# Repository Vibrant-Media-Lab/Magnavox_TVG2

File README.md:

# Ralph Baer's TV Game Version 2

Ralph Henry Baer, "the Father of Video Games", engineered the first home video game console, licensed by Magnavox as the Magnavox Odyssey.
Before the Odyssey came along, there were 3 prototypes, named TV Game 1, TV Game 2 and TV Game 3 "The Brown Box". The world famous Atari 
game _"Pong"_ is inspired by the _Table Tennis_ game available on the Brown Box and Odyssey.

This repository contains a true-to-original replica of the TV Game 2 video game console, drafted by Ralph in 1967. Thanks to the support from 
the Smithsonian Institute, we are able to obtain the original paper-based schematics, game overlays and an enclosure replica.

The finished unit will be on display in University of Pittsburgh's Vibrant Media Lab, headed by Dr. Zachary Horton.

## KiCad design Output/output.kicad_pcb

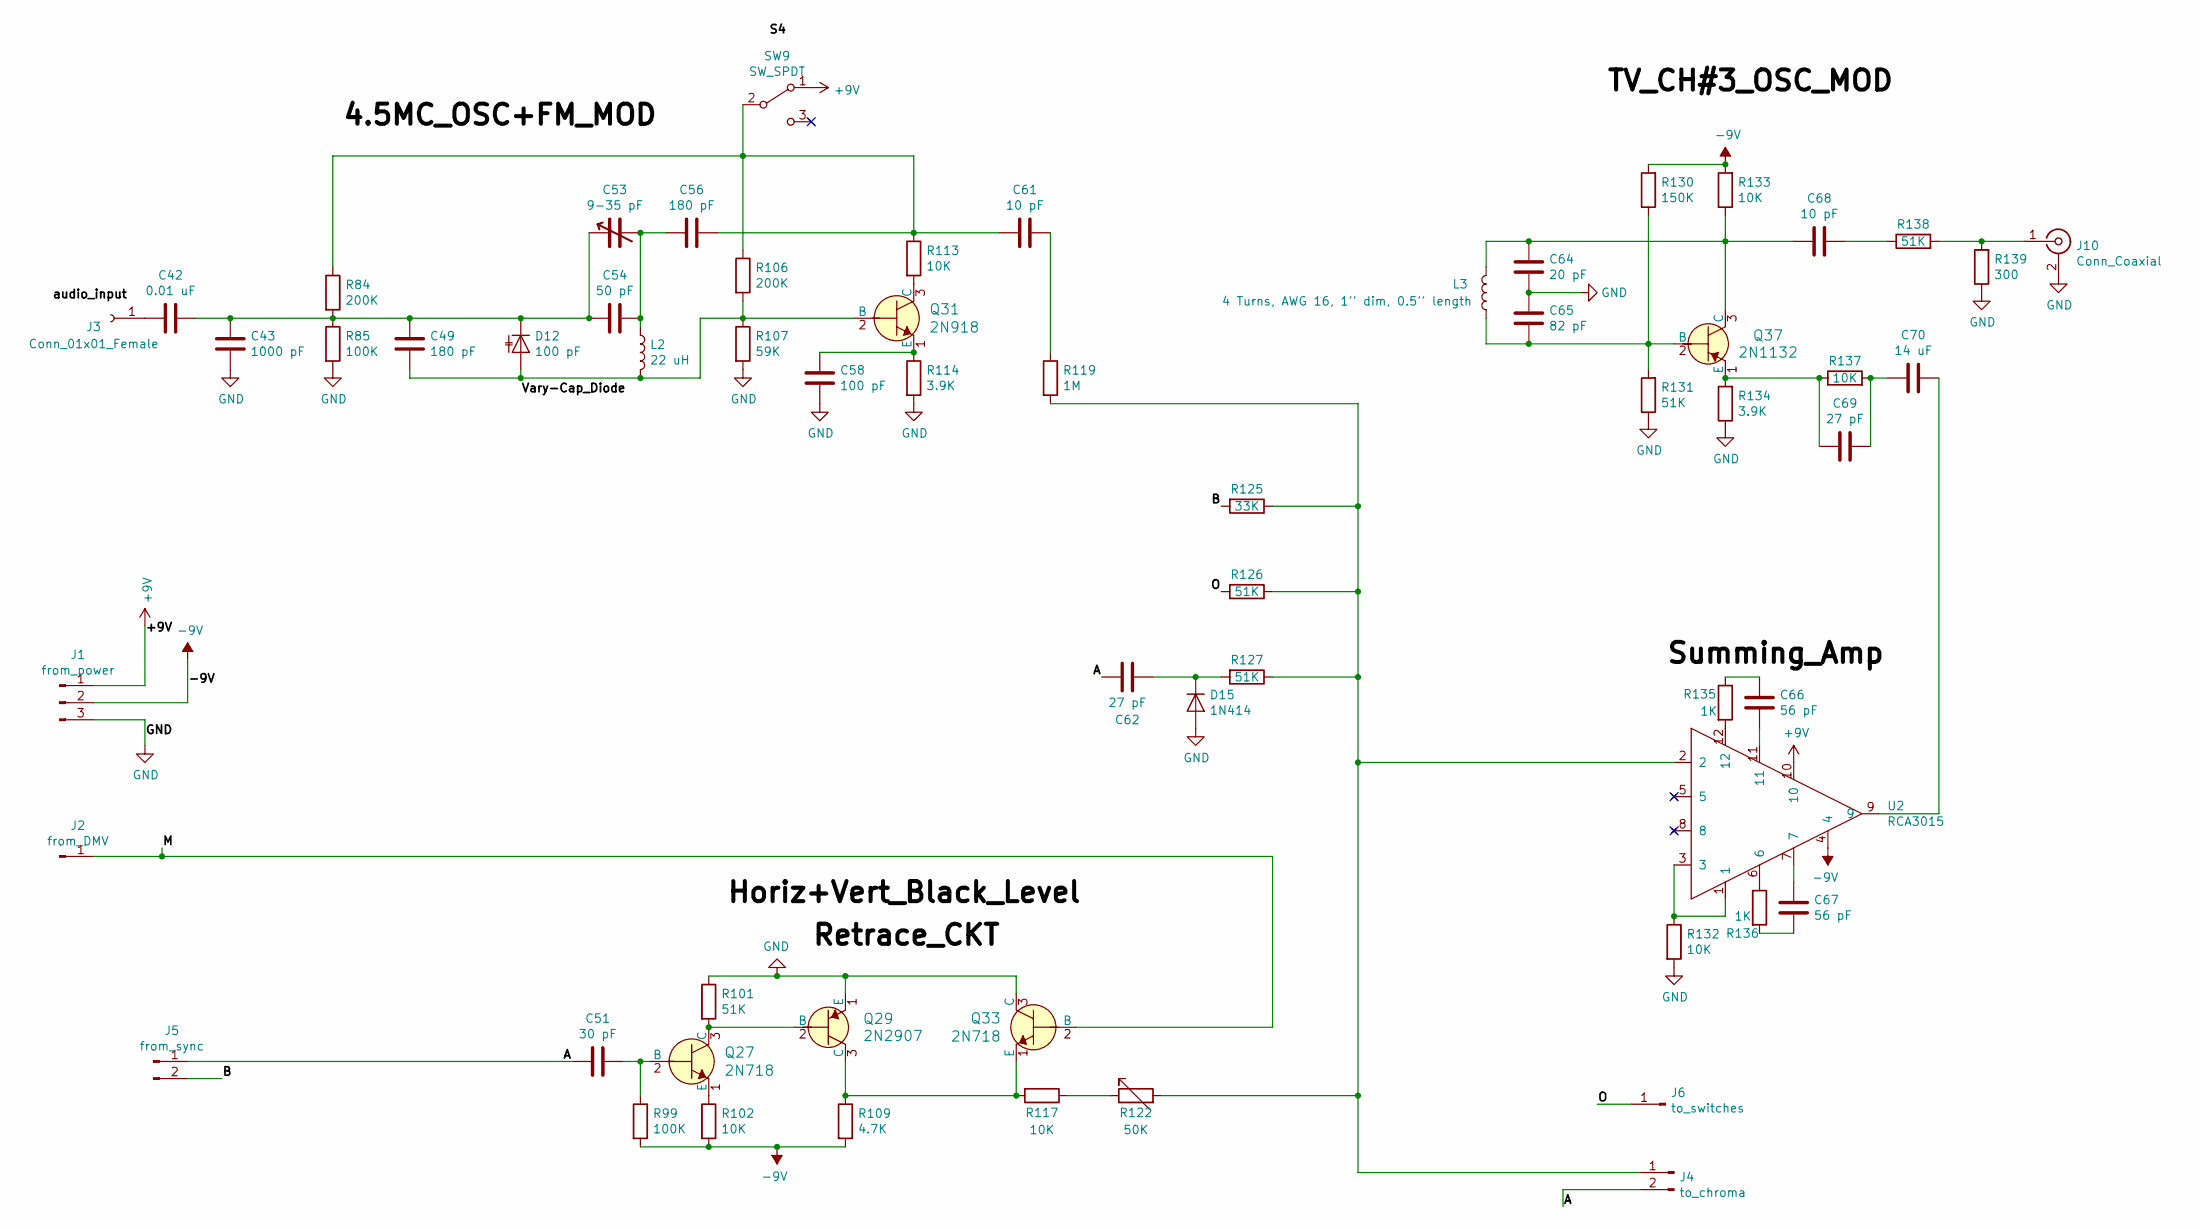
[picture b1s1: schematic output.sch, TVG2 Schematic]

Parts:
C42: 0.01 uF; C_Disc_D4.7mm_W2.5mm_P5.00mm
C43: 1000 pF; C_Disc_D4.7mm_W2.5mm_P5.00mm
C49, C56: 180 pF; C_Disc_D4.7mm_W2.5mm_P5.00mm
C51: 30 pF; C_Disc_D4.7mm_W2.5mm_P5.00mm
C53: 9-35 pF; 9-35pF_Trim
C54: 50 pF; C_Disc_D4.7mm_W2.5mm_P5.00mm
C58: 100 pF; C_Disc_D4.7mm_W2.5mm_P5.00mm
C61, C68: 10 pF; C_Disc_D4.7mm_W2.5mm_P5.00mm
C62, C69: 27 pF; C_Disc_D4.7mm_W2.5mm_P5.00mm
C64: 20 pF; C_Disc_D4.7mm_W2.5mm_P5.00mm
C65: 82 pF; C_Disc_D4.7mm_W2.5mm_P5.00mm
C66, C67: 56 pF; C_Disc_D4.7mm_W2.5mm_P5.00mm
C70: 14 uF; CP_Radial_D5.0mm_P2.00mm
D12: 100 pF; PinSocket_1x02_P2.54mm_Vertical
D15: 1N414; D_DO-41_SOD81_P10.16mm_Horizontal
J1: from_power; PinHeader_1x03_P2.54mm_Vertical
J2: from_DMV; PinHeader_1x01_P2.54mm_Vertical
J3: Conn_01x01_Female; PinSocket_1x01_P2.54mm_Vertical
J4: to_chroma; PinHeader_1x02_P2.54mm_Vertical
J5: from_sync; PinHeader_1x02_P2.54mm_Vertical
J6: to_switches; PinHeader_1x01_P2.54mm_Vertical
J10: Conn_Coaxial; PinSocket_1x02_P2.54mm_Vertical
L2: 22 uH; R_Axial_DIN0207_L6.3mm_D2.5mm_P7.62mm_Horizontal
L3: 4 Turns, AWG 16, 1'' dim, 0.5'' length; PinSocket_1x02_P2.54mm_Vertical
Q27, Q33: 2N718; TO-92-3; MPN 2N5109; Digi-Key_PN 2N5109CS-ND
Q29: 2N2907; TO-92-3; MPN 2N2907A; Digi-Key_PN 2N2907ACS-ND
Q31: 2N918; TO-92-3; MPN 2N5109; Digi-Key_PN 2N5109CS-ND
Q37: 2N1132; TO-92-3; MPN 2N2222; Digi-Key_PN 2N2222CS-ND
R84, R106: 200K; R_Axial_DIN0207_L6.3mm_D2.5mm_P7.62mm_Horizontal
R85, R99: 100K; R_Axial_DIN0207_L6.3mm_D2.5mm_P7.62mm_Horizontal
R101, R126, R127, R131, R138: 51K; R_Axial_DIN0207_L6.3mm_D2.5mm_P7.62mm_Horizontal
R102, R113, R117, R132, R133, R137: 10K; R_Axial_DIN0207_L6.3mm_D2.5mm_P7.62mm_Horizontal
R107: 59K; R_Axial_DIN0207_L6.3mm_D2.5mm_P7.62mm_Horizontal
R109: 4.7K; R_Axial_DIN0207_L6.3mm_D2.5mm_P7.62mm_Horizontal
R114, R134: 3.9K; R_Axial_DIN0207_L6.3mm_D2.5mm_P7.62mm_Horizontal
R119: 1M; R_Axial_DIN0207_L6.3mm_D2.5mm_P7.62mm_Horizontal
R122: 50K; Potentiometer_Bourns_3386F_Vertical
R125: 33K; R_Axial_DIN0207_L6.3mm_D2.5mm_P7.62mm_Horizontal
R130: 150K; R_Axial_DIN0207_L6.3mm_D2.5mm_P7.62mm_Horizontal
R135, R136: 1K; R_Axial_DIN0207_L6.3mm_D2.5mm_P7.62mm_Horizontal
R139: 300; R_Axial_DIN0207_L6.3mm_D2.5mm_P7.62mm_Horizontal
SW9: SW_SPDT; Toggle_Switch_100SP1T1B4M2QE
U2: RCA3015; TO-5-12

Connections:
+9V: J1.1, SW9.1 (A), U2.10
-9V: J1.2, R99.2, R102.2, R109.2, R130.2, R133.2, U2.4
/A: C51.2, C62.1, J4.2, J5.1
/B: J5.2, R125.2
/M: J2.1, Q33.2 (B)
/O: J6.1, R126.2
GND: C43.1, C58.1, C64.2, C65.1, D15.2 (A), J1.3, J10.2 (Ext), Q29.1 (E), Q33.3 (C), R85.2, R101.1, R107.2, R114.2, R131.1, R132.2, R134.1, R139.1
unnamed: C42.1, C43.2, C49.2, C53.1, C54.1, D12.1 (K), R84.2, R85.1
unnamed: C42.2, J3.1
unnamed: C49.1, D12.2 (A), L2.2, Q31.2 (B), R106.2, R107.1
unnamed: C51.1, Q27.2 (B), R99.1
unnamed: C53.2, C54.2, C56.1, L2.1
unnamed: C56.2, C61.2, R84.1, R106.1, R113.1, SW9.2 (B)
unnamed: C58.2, Q31.1 (E), R114.1
unnamed: C61.1, R119.1
unnamed: C62.2, D15.1 (K), R127.2
unnamed: C64.1, C68.2, L3.2, Q37.3 (C), R133.1
unnamed: C65.2, L3.1, Q37.2 (B), R130.1, R131.2
unnamed: C66.1, R135.1
unnamed: C66.2, U2.11
unnamed: C67.1, U2.7
unnamed: C67.2, R136.2
unnamed: C68.1, R138.1
unnamed: C69.1, C70.2, R137.2
unnamed: C69.2, Q37.1 (E), R134.2, R137.1
unnamed: C70.1, U2.9
unnamed: J4.1, R119.2, R122.2, R125.1, R126.1, R127.1, U2.2
unnamed: J10.1 (In), R138.2, R139.2
unnamed: Q27.1 (E), R102.1
unnamed: Q27.3 (C), Q29.2 (B), R101.2
unnamed: Q29.3 (C), Q33.1 (E), R109.1, R117.2
unnamed: Q31.3 (C), R113.2
unnamed: R117.1, R122.1
unnamed: R132.1, U2.1, U2.3
unnamed: R135.2, U2.12
unnamed: R136.1, U2.6

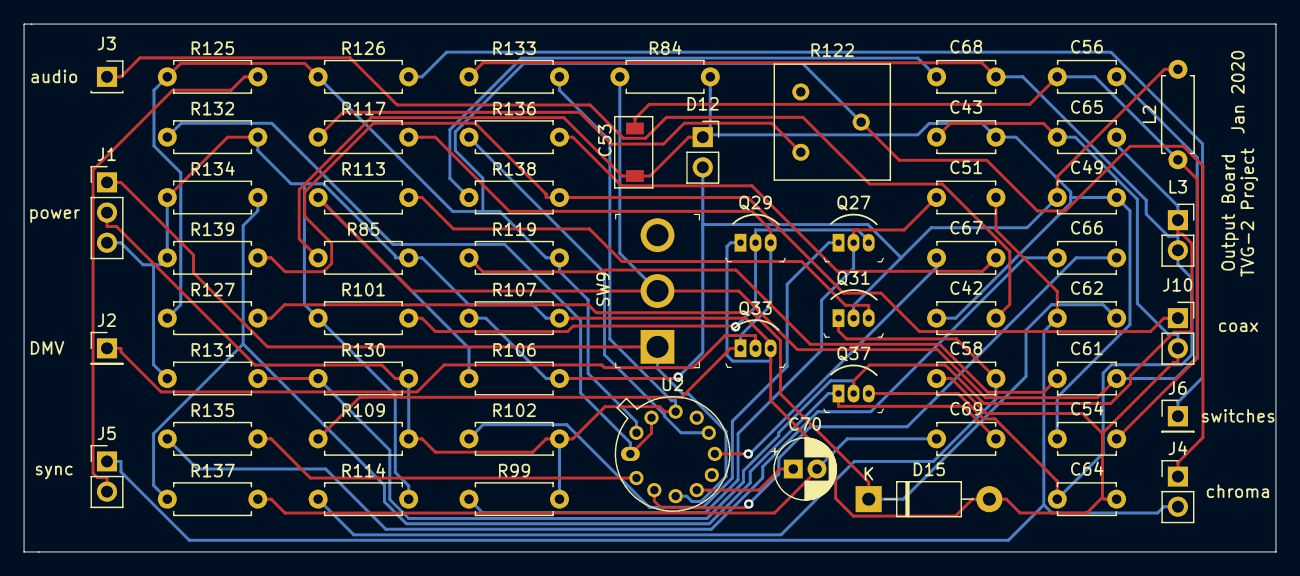
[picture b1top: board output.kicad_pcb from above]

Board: 2 copper layers, 105.4 x 44.5 mm, 61 parts (0 on the bottom side), 36 nets.

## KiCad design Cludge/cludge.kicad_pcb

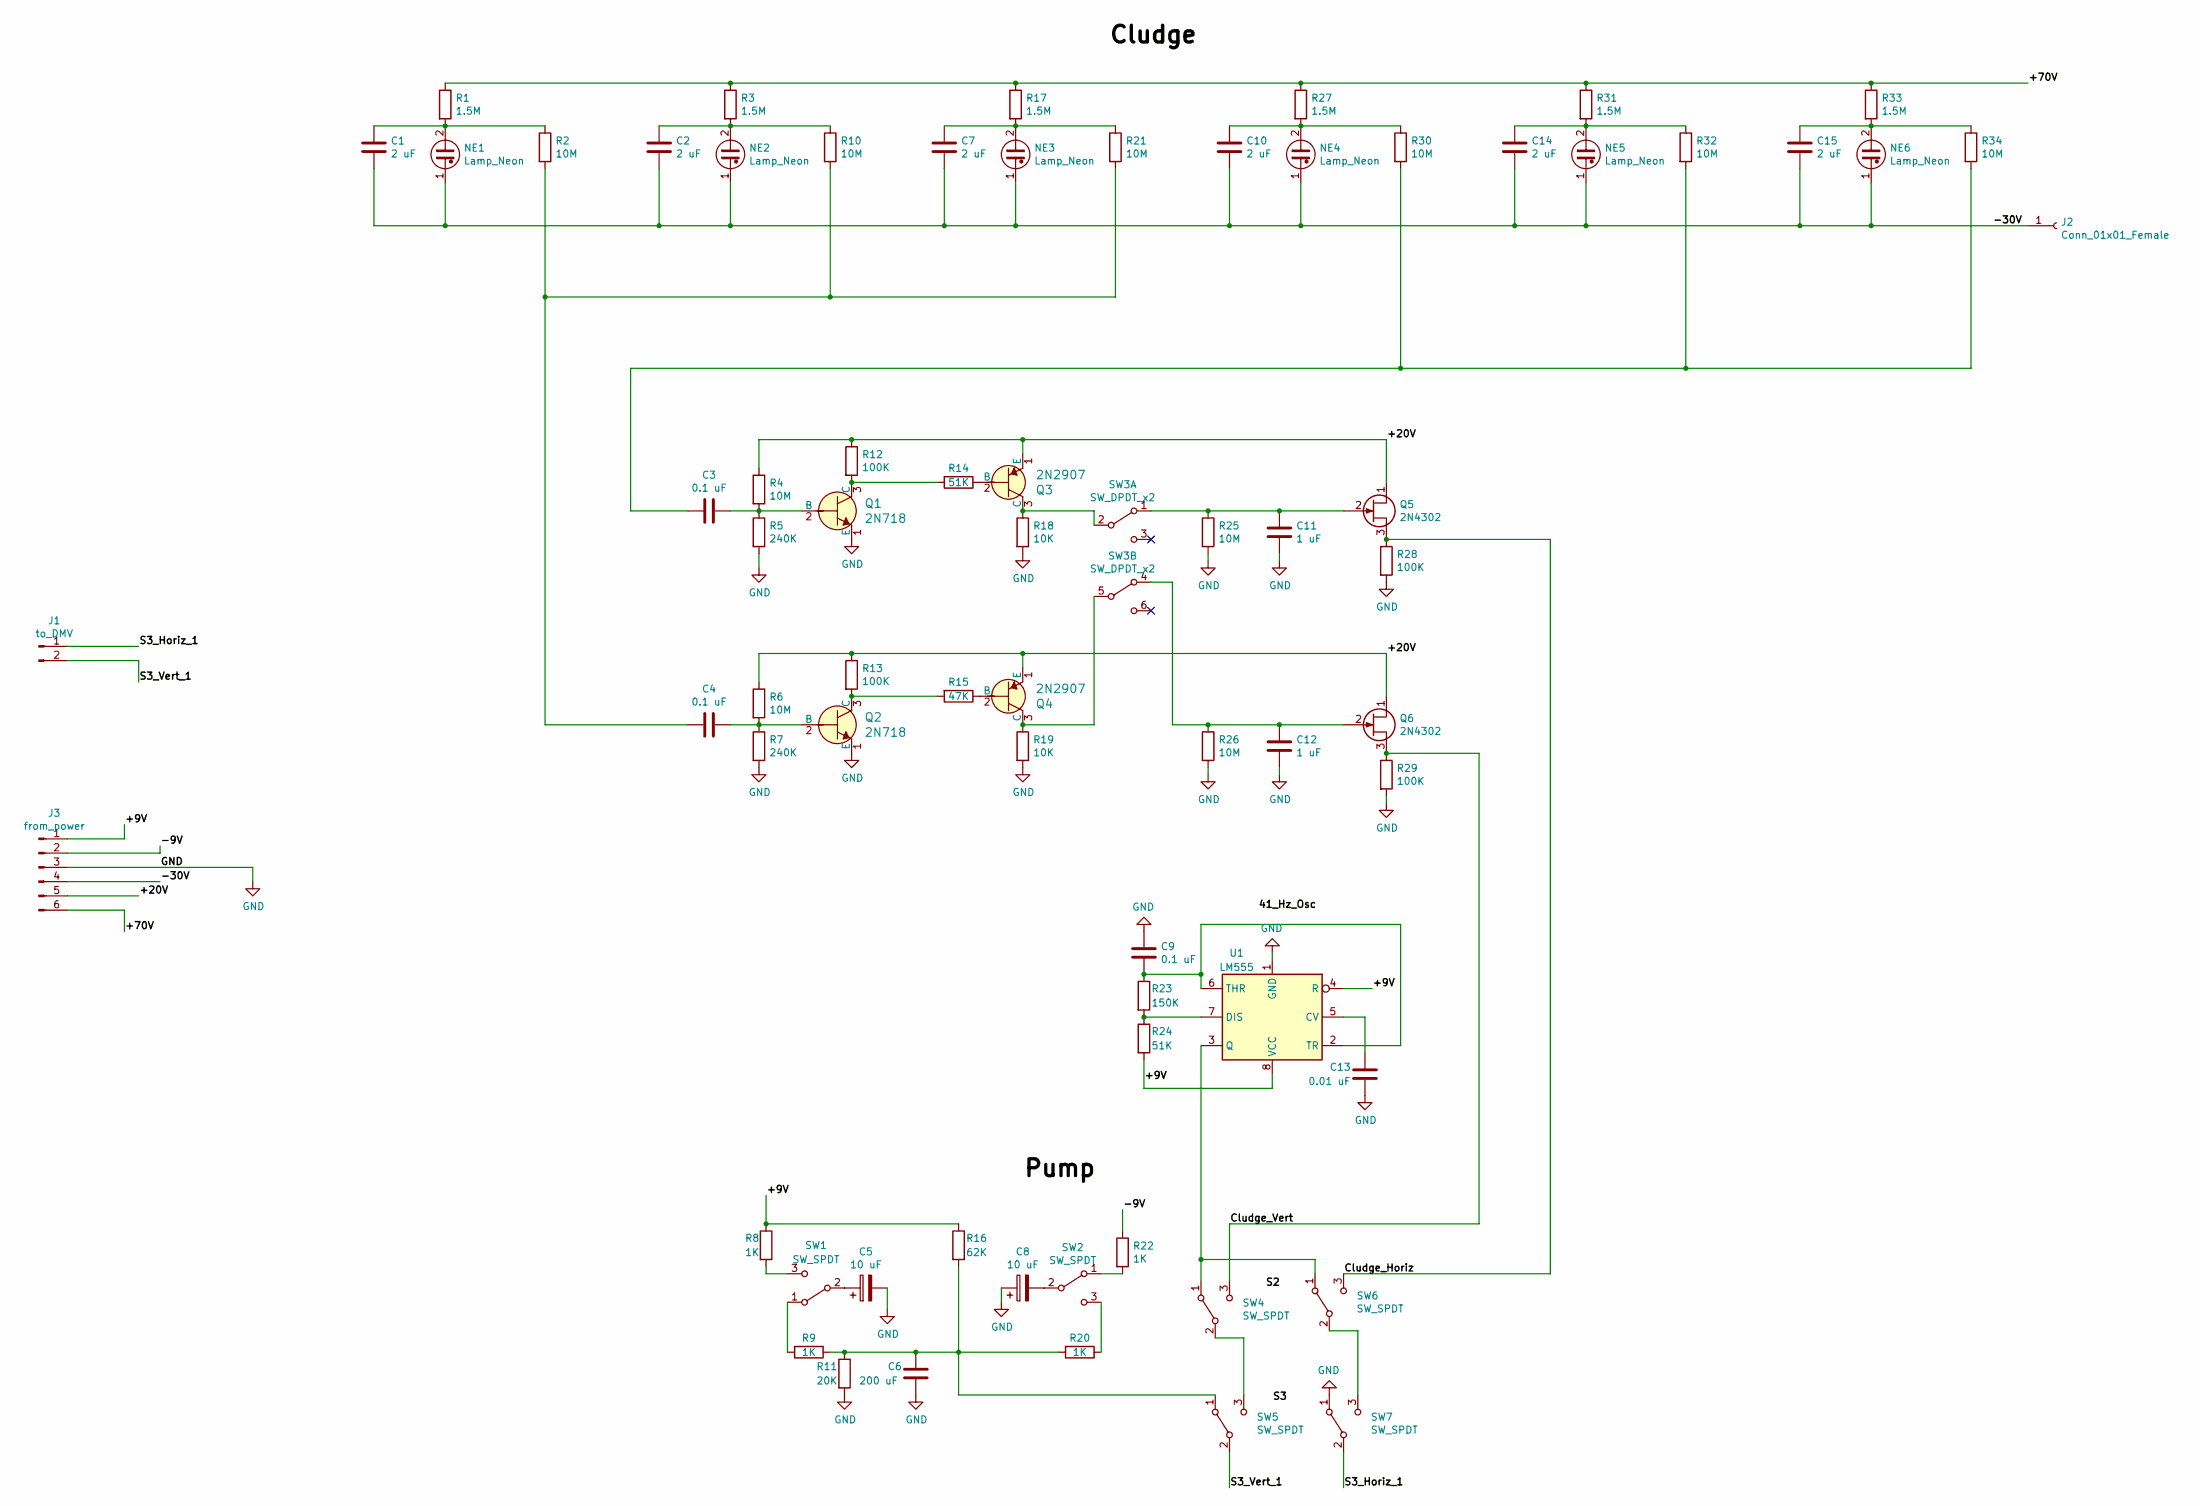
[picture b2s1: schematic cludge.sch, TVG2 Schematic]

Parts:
C1, C2, C7, C10, C14, C15: 2 uF; C_Disc_D4.7mm_W2.5mm_P5.00mm
C3, C4, C9: 0.1 uF; C_Disc_D4.7mm_W2.5mm_P5.00mm
C5, C8: 10 uF; CP_Radial_D5.0mm_P2.00mm
C6: 200 uF; CP_Radial_D14.0mm_P5.00mm
C11, C12: 1 uF; C_Disc_D4.7mm_W2.5mm_P5.00mm
C13: 0.01 uF; C_Disc_D4.7mm_W2.5mm_P5.00mm
J1: to_DMV; PinHeader_1x02_P2.54mm_Vertical
J2: Conn_01x01_Female; PinSocket_1x01_P2.54mm_Vertical
J3: from_power; PinHeader_1x06_P2.54mm_Vertical
NE1, NE2, NE3, NE4, NE5, NE6: Lamp_Neon; PinSocket_1x02_P2.54mm_Vertical
Q1, Q2: 2N718; TO-92-3; MPN 2N5109; Digi-Key_PN 2N5109CS-ND
Q3, Q4: 2N2907; TO-92-3; MPN 2N2907A; Digi-Key_PN 2N2907ACS-ND
Q5, Q6: 2N4302; TO-92-3
R1, R3, R17, R27, R31, R33: 1.5M; R_Axial_DIN0207_L6.3mm_D2.5mm_P7.62mm_Horizontal
R2, R4, R6, R10, R21, R25, R26, R30, R32, R34: 10M; R_Axial_DIN0207_L6.3mm_D2.5mm_P7.62mm_Horizontal
R5, R7: 240K; R_Axial_DIN0207_L6.3mm_D2.5mm_P7.62mm_Horizontal
R8, R9, R20, R22: 1K; R_Axial_DIN0207_L6.3mm_D2.5mm_P7.62mm_Horizontal
R11: 20K; R_Axial_DIN0207_L6.3mm_D2.5mm_P7.62mm_Horizontal
R12, R13, R28, R29: 100K; R_Axial_DIN0207_L6.3mm_D2.5mm_P7.62mm_Horizontal
R14, R24: 51K; R_Axial_DIN0207_L6.3mm_D2.5mm_P7.62mm_Horizontal
R15: 47K; R_Axial_DIN0207_L6.3mm_D2.5mm_P7.62mm_Horizontal
R16: 62K; R_Axial_DIN0207_L6.3mm_D2.5mm_P7.62mm_Horizontal
R18, R19: 10K; R_Axial_DIN0207_L6.3mm_D2.5mm_P7.62mm_Horizontal
R23: 150K; R_Axial_DIN0207_L6.3mm_D2.5mm_P7.62mm_Horizontal
SW1, SW2, SW4, SW5, SW6, SW7: SW_SPDT; Toggle_Switch_100SP1T1B4M2QE
SW3: SW_DPDT_x2; TVG2_Cludge_DPDT_Switch
U1: LM555; DIP-8_W7.62mm

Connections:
/+9V: J3.1, R8.1, R16.1, R24.2, U1.4 (R), U1.8 (VCC)
/+20V: J3.5, Q3.1 (E), Q4.1 (E), Q5.1 (D), Q6.1 (D), R4.1, R6.1, R12.1, R13.1
/+70V: J3.6, R1.1, R3.1, R17.1, R27.1, R31.1, R33.1
/-9V: J3.2, R22.1
/-30V: C1.2, C2.2, C7.2, C10.2, C14.2, C15.2, J2.1, J3.4, NE1.1, NE2.1, NE3.1, NE4.1, NE5.1, NE6.1
/Cludge_Horiz: Q5.3 (S), R28.1, SW6.3 (C)
/Cludge_Vert: Q6.3 (S), R29.1, SW4.3 (C)
/S3_Horiz_1: J1.1, SW7.2 (B)
/S3_Vert_1: J1.2, SW5.2 (B)
GND: C5.2, C6.2, C8.1, C9.1, C11.1, C12.1, C13.2, J3.3, Q1.1 (E), Q2.1 (E), R5.2, R7.2, R11.2, R18.2, R19.2, R25.2, R26.2, R28.2, R29.2, SW7.1 (A), U1.1 (GND)
unnamed: C1.1, NE1.2, R1.2, R2.1
unnamed: C2.1, NE2.2, R3.2, R10.1
unnamed: C3.1, Q1.2 (B), R4.2, R5.1
unnamed: C3.2, R30.2, R32.2, R34.2
unnamed: C4.1, Q2.2 (B), R6.2, R7.1
unnamed: C4.2, R2.2, R10.2, R21.2
unnamed: C5.1, SW1.2 (B)
unnamed: C6.1, R9.1, R11.1, R16.2, R20.2, SW5.1 (A)
unnamed: C7.1, NE3.2, R17.2, R21.1
unnamed: C8.2, SW2.2 (B)
unnamed: C9.2, R23.1, U1.2 (TR), U1.6 (THR)
unnamed: C10.1, NE4.2, R27.2, R30.1
unnamed: C11.2, Q5.2 (G), R25.1, SW3.1 (A)
unnamed: C12.2, Q6.2 (G), R26.1, SW3.4 (A)
unnamed: C13.1, U1.5 (CV)
unnamed: C14.1, NE5.2, R31.2, R32.1
unnamed: C15.1, NE6.2, R33.2, R34.1
unnamed: Q1.3 (C), R12.2, R14.2
unnamed: Q2.3 (C), R13.2, R15.2
unnamed: Q3.2 (B), R14.1
unnamed: Q3.3 (C), R18.1, SW3.2 (B)
unnamed: Q4.2 (B), R15.1
unnamed: Q4.3 (C), R19.1, SW3.5 (B)
unnamed: R8.2, SW1.3 (C)
unnamed: R9.2, SW1.1 (A)
unnamed: R20.1, SW2.3 (C)
unnamed: R22.2, SW2.1 (A)
unnamed: R23.2, R24.1, U1.7 (DIS)
unnamed: SW4.1 (A), SW6.1 (A), U1.3 (Q)
unnamed: SW4.2 (B), SW5.3 (C)
unnamed: SW6.2 (B), SW7.3 (C)

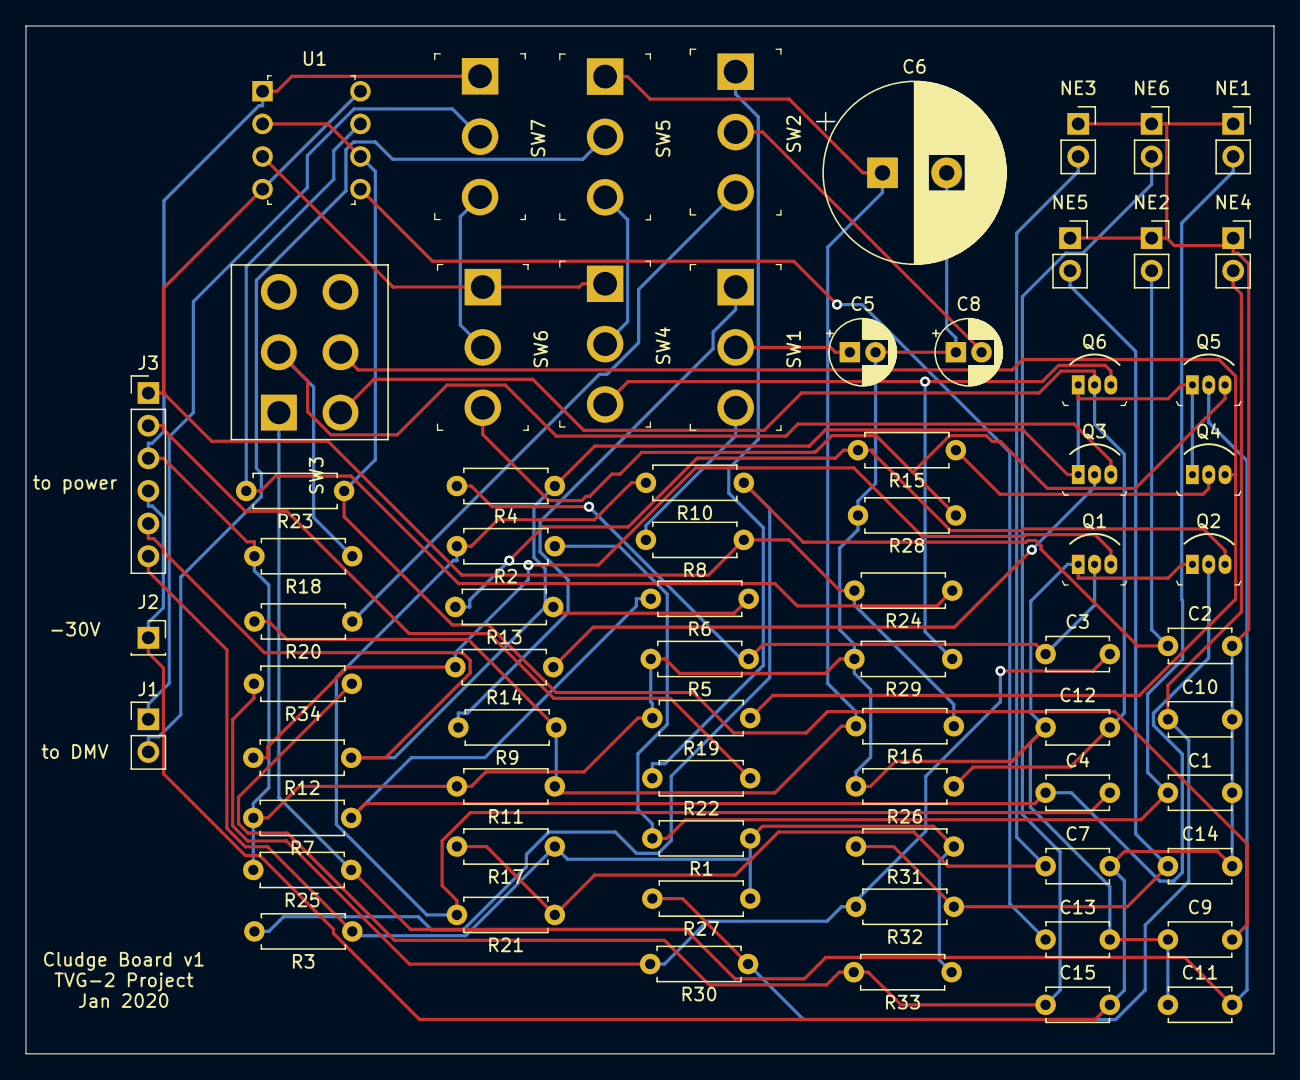
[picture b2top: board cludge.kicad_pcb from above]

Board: 2 copper layers, 97.2 x 80.0 mm, 72 parts (0 on the bottom side), 41 nets.

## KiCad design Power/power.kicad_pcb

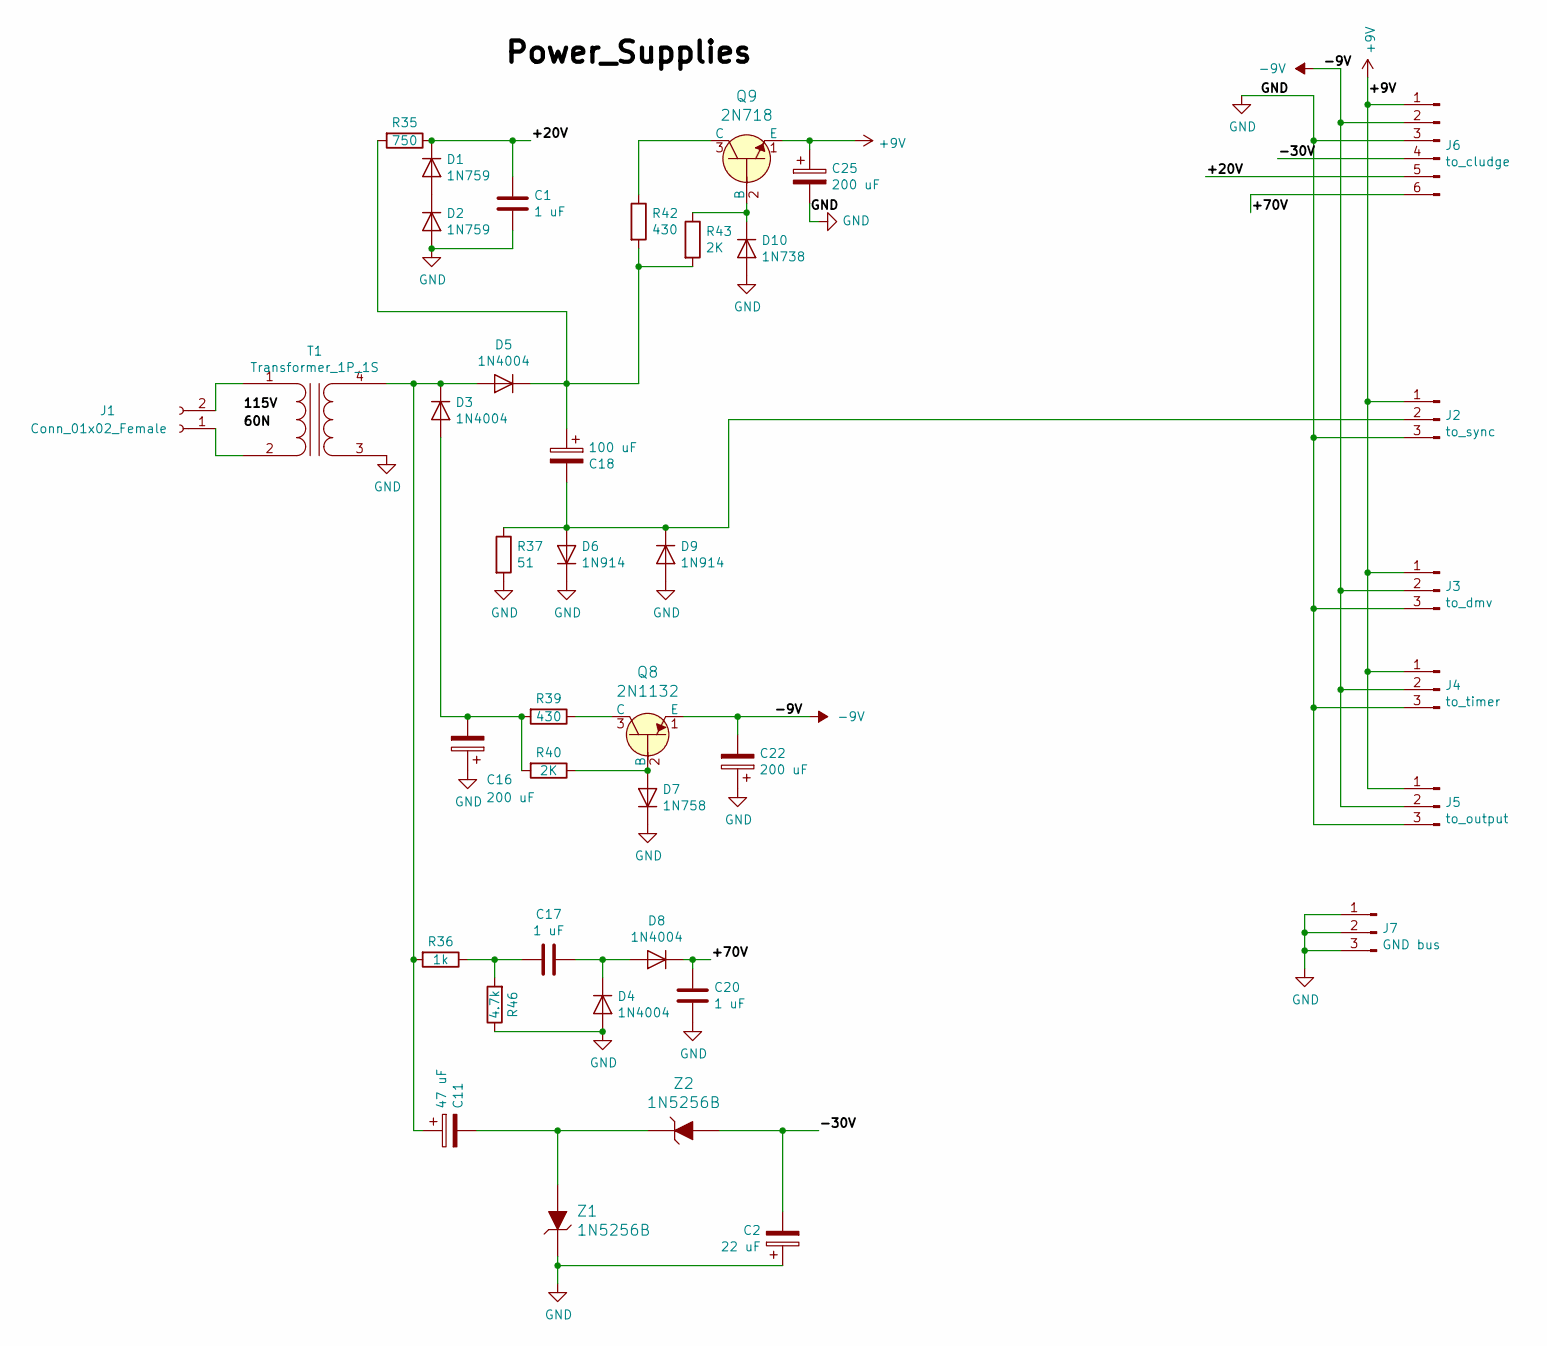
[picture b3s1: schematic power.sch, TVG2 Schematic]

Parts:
C1: 1 uF; CP_Radial_D10.0mm_P3.80mm
C2: 22 uF; CP_Radial_D10.0mm_P3.80mm
C11: 47 uF; CP_Radial_D10.0mm_P3.80mm
C16, C22, C25: 200 uF; CP_Radial_D14.0mm_P5.00mm
C17, C20: 1 uF; C_Disc_D4.7mm_W2.5mm_P5.00mm
C18: 100 uF; CP_Radial_D10.0mm_P3.80mm
D1, D2: 1N759; D_DO-41_SOD81_P10.16mm_Horizontal
D3, D4, D5, D8: 1N4004; D_DO-41_SOD81_P10.16mm_Horizontal
D6, D9: 1N914; D_DO-41_SOD81_P10.16mm_Horizontal
D7: 1N758; D_DO-41_SOD81_P10.16mm_Horizontal
D10: 1N738; D_DO-41_SOD81_P10.16mm_Horizontal
J1: Conn_01x02_Female; PinSocket_1x02_P2.54mm_Vertical
J2: to_sync; PinHeader_1x03_P2.54mm_Vertical
J3: to_dmv; PinHeader_1x03_P2.54mm_Vertical
J4: to_timer; PinHeader_1x03_P2.54mm_Vertical
J5: to_output; PinHeader_1x03_P2.54mm_Vertical
J6: to_cludge; PinHeader_1x06_P2.54mm_Vertical
J7: GND bus; PinHeader_1x03_P2.54mm_Vertical
Q8: 2N1132; TO-92-3; MPN 2N2222; Digi-Key_PN 2N2222CS-ND
Q9: 2N718; TO-92-3; MPN 2N5109; Digi-Key_PN 2N5109CS-ND
R35: 750; R_Axial_DIN0207_L6.3mm_D2.5mm_P7.62mm_Horizontal
R36: 1k; R_Axial_DIN0207_L6.3mm_D2.5mm_P7.62mm_Horizontal
R37: 51; R_Axial_DIN0207_L6.3mm_D2.5mm_P7.62mm_Horizontal
R39, R42: 430; R_Axial_DIN0207_L6.3mm_D2.5mm_P7.62mm_Horizontal
R40, R43: 2K; R_Axial_DIN0207_L6.3mm_D2.5mm_P7.62mm_Horizontal
R46: 4.7k; R_Axial_DIN0207_L6.3mm_D2.5mm_P7.62mm_Horizontal
T1: Transformer_1P_1S; PinSocket_1x04_P2.54mm_Vertical
Z1, Z2: 1N5256B; DO-41; MPN MMSZ5231B-7-F; Digi-Key_PN MMSZ5231B-FDICT-ND

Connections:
+9V: C25.1, J2.1, J3.1, J4.1, J5.1, J6.1, Q9.1 (E)
-9V: C22.2, J3.2, J4.2, J5.2, J6.2, Q8.1 (E)
/+20V: C1.2, D1.1 (K), J6.5, R35.1
/+70V: C20.1, D8.1 (K), J6.6
/-30V: C2.2, J6.4, Z2.A
GND: C1.1, C2.1, C16.1, C20.2, C22.1, C25.2, D2.2 (A), D4.2 (A), D6.1 (K), D7.1 (K), D9.2 (A), D10.2 (A), J2.3, J3.3, J4.3, J5.3, J6.3, J7.1, J7.2, J7.3, R37.2, R46.1, T1.3 (SA), Z1.K
unnamed: C11.1, D3.1 (K), D5.2 (A), R36.2, T1.4 (SB)
unnamed: C11.2, Z1.A, Z2.K
unnamed: C16.2, D3.2 (A), R39.2, R40.2
unnamed: C17.1, R36.1, R46.2
unnamed: C17.2, D4.1 (K), D8.2 (A)
unnamed: C18.1, D5.1 (K), R35.2, R42.2, R43.2
unnamed: C18.2, D6.2 (A), D9.1 (K), J2.2, R37.1
unnamed: D1.2 (A), D2.1 (K)
unnamed: D7.2 (A), Q8.2 (B), R40.1
unnamed: D10.1 (K), Q9.2 (B), R43.1
unnamed: J1.1, T1.2 (AB)
unnamed: J1.2, T1.1 (AA)
unnamed: Q8.3 (C), R39.1
unnamed: Q9.3 (C), R42.1

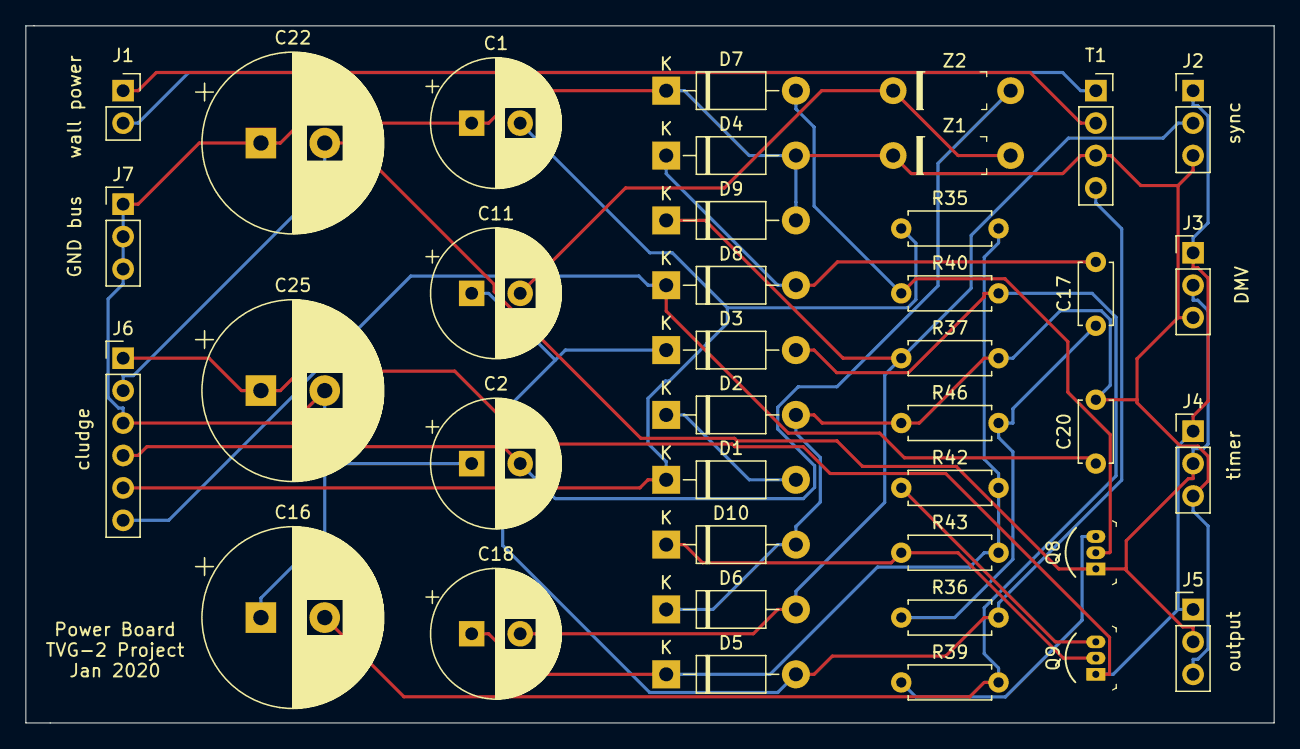
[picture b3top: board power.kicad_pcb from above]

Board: 2 copper layers, 97.8 x 54.6 mm, 39 parts (0 on the bottom side), 20 nets.

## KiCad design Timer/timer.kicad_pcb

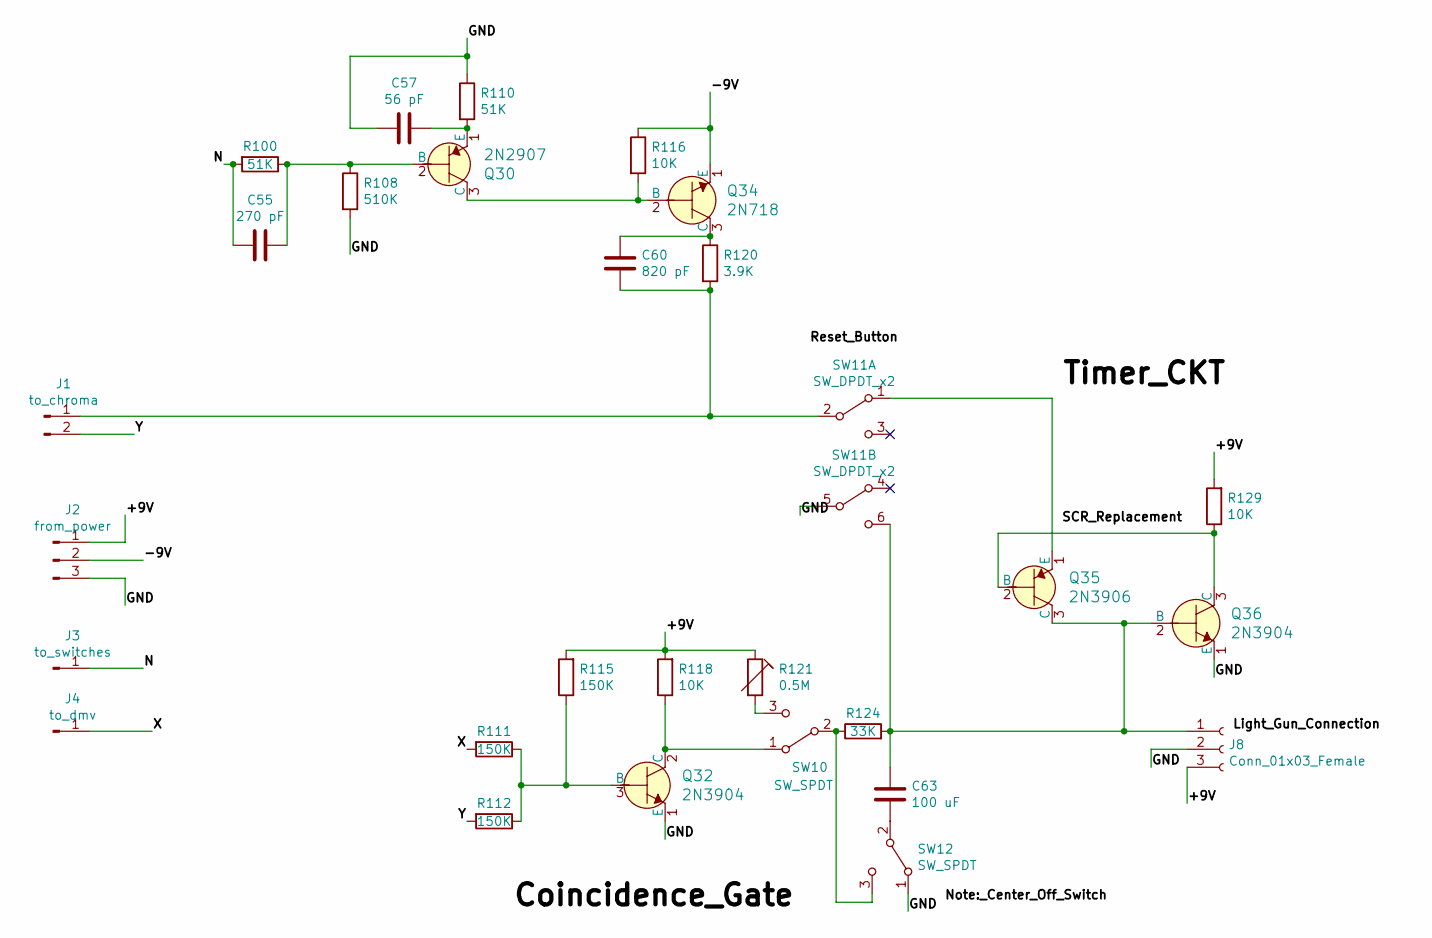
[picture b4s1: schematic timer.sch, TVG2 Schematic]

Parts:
C55: 270 pF; C_Disc_D4.7mm_W2.5mm_P5.00mm
C57: 56 pF; C_Disc_D4.7mm_W2.5mm_P5.00mm
C60: 820 pF; C_Disc_D4.7mm_W2.5mm_P5.00mm
C63: 100 uF; CP_Radial_D10.0mm_P3.50mm
J1: to_chroma; PinHeader_1x02_P2.54mm_Vertical
J2: from_power; PinHeader_1x03_P2.54mm_Vertical
J3: to_switches; PinHeader_1x01_P2.54mm_Vertical
J4: to_dmv; PinHeader_1x01_P2.54mm_Vertical
J8: Conn_01x03_Female; PinSocket_1x03_P2.54mm_Vertical
Q30: 2N2907; TO-92-3; MPN 2N2907A; Digi-Key_PN 2N2907ACS-ND
Q32: 2N3904; TO-92-3; MPN 2N3904; Digi-Key_PN 2N3904CS-ND
Q34: 2N718; TO-92-3; MPN 2N5109; Digi-Key_PN 2N5109CS-ND
Q35: 2N3906; TO-92-3; MPN 2N3906; Digi-Key_PN 2N3906CS-ND
Q36: 2N3904; TO-92-3; MPN 2N5109; Digi-Key_PN 2N5109CS-ND
R100, R110: 51K; R_Axial_DIN0207_L6.3mm_D2.5mm_P7.62mm_Horizontal
R108: 510K; R_Axial_DIN0207_L6.3mm_D2.5mm_P7.62mm_Horizontal
R111, R112, R115: 150K; R_Axial_DIN0207_L6.3mm_D2.5mm_P7.62mm_Horizontal
R116, R118, R129: 10K; R_Axial_DIN0207_L6.3mm_D2.5mm_P7.62mm_Horizontal
R120: 3.9K; R_Axial_DIN0207_L6.3mm_D2.5mm_P7.62mm_Horizontal
R121: 0.5M; Potentiometer_Bourns_3386F_Vertical
R124: 33K; R_Axial_DIN0207_L6.3mm_D2.5mm_P7.62mm_Horizontal
SW10, SW12: SW_SPDT; Toggle_Switch_100SP1T1B4M2QE
SW11: SW_DPDT_x2; TVG2_Pushbutton

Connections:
/+9V: J2.1, J8.3, R115.2, R118.2, R121.1, R129.2
/-9V: J2.2, Q34.1 (E), R116.1
/GND: C57.2, J2.3, J8.2, Q32.1 (E), Q36.1 (E), R108.2, R110.1, SW11.5 (B), SW12.1 (A)
/N: C55.2, J3.1, R100.2
/X: J4.1, R111.2
/Y: J1.2, R112.2
unnamed: C55.1, Q30.2 (B), R100.1, R108.1
unnamed: C57.1, Q30.1 (E), R110.2
unnamed: C60.1, Q34.3 (C), R120.1
unnamed: C60.2, J1.1, R120.2, SW11.2 (B)
unnamed: C63.1, J8.1, Q35.3 (C), Q36.2 (B), R124.2, SW11.6 (C)
unnamed: C63.2, SW12.2 (B)
unnamed: Q30.3 (C), Q34.2 (B), R116.2
unnamed: Q32.2 (C), R118.1, SW10.1 (A)
unnamed: Q32.3 (B), R111.1, R112.1, R115.1
unnamed: Q35.1 (E), SW11.1 (A)
unnamed: Q35.2 (B), Q36.3 (C), R129.1
unnamed: R121.2, SW10.3 (C)
unnamed: R124.1, SW10.2 (B), SW12.3 (C)

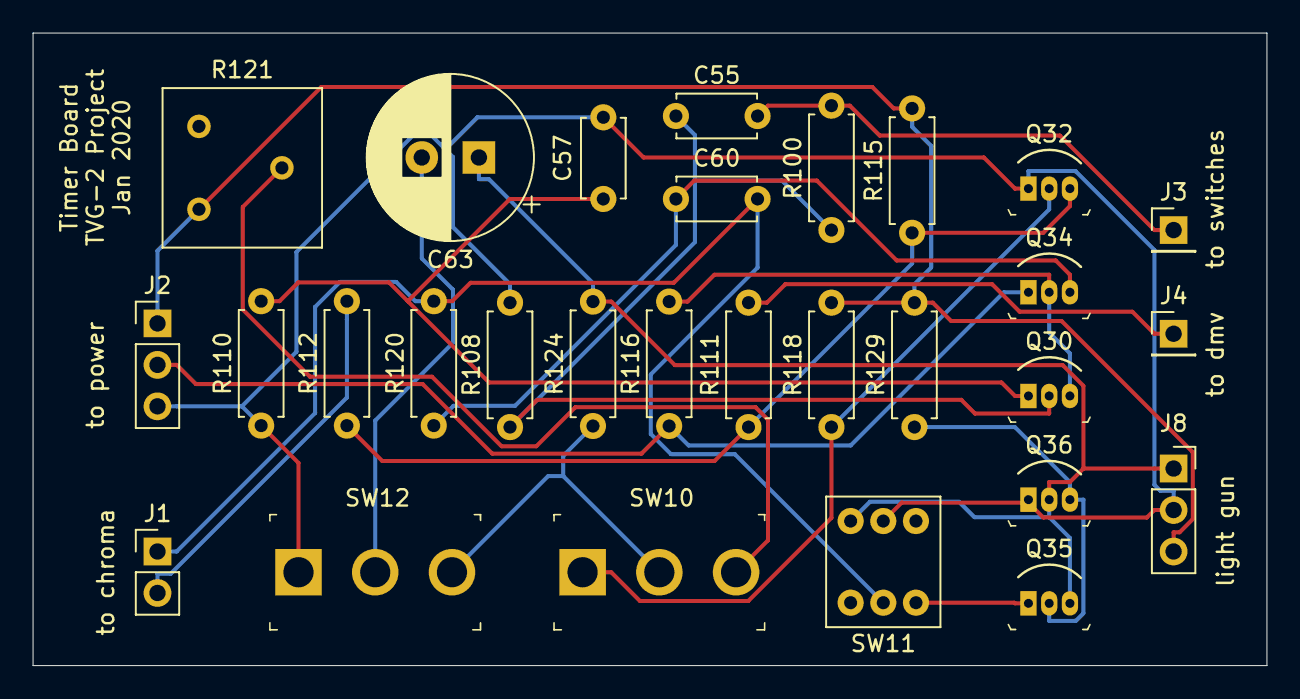
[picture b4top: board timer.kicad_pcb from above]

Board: 2 copper layers, 75.6 x 38.7 mm, 29 parts (0 on the bottom side), 19 nets.
